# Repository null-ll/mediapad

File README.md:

# mediapad

A simple 3d printed volume/media controller macropad with 3 MX-style keyswitches and 8 customizable WS2812B RGB LEDs! Runs on [QMK firmware](https://github.com/qmk/qmk_firmware).

Case is still a WIP. Current version requires drilling holes into the top housing for the screws. The USB cutout also seems a bit off but that could just be poor tolerances from my 3d printer.

# usage

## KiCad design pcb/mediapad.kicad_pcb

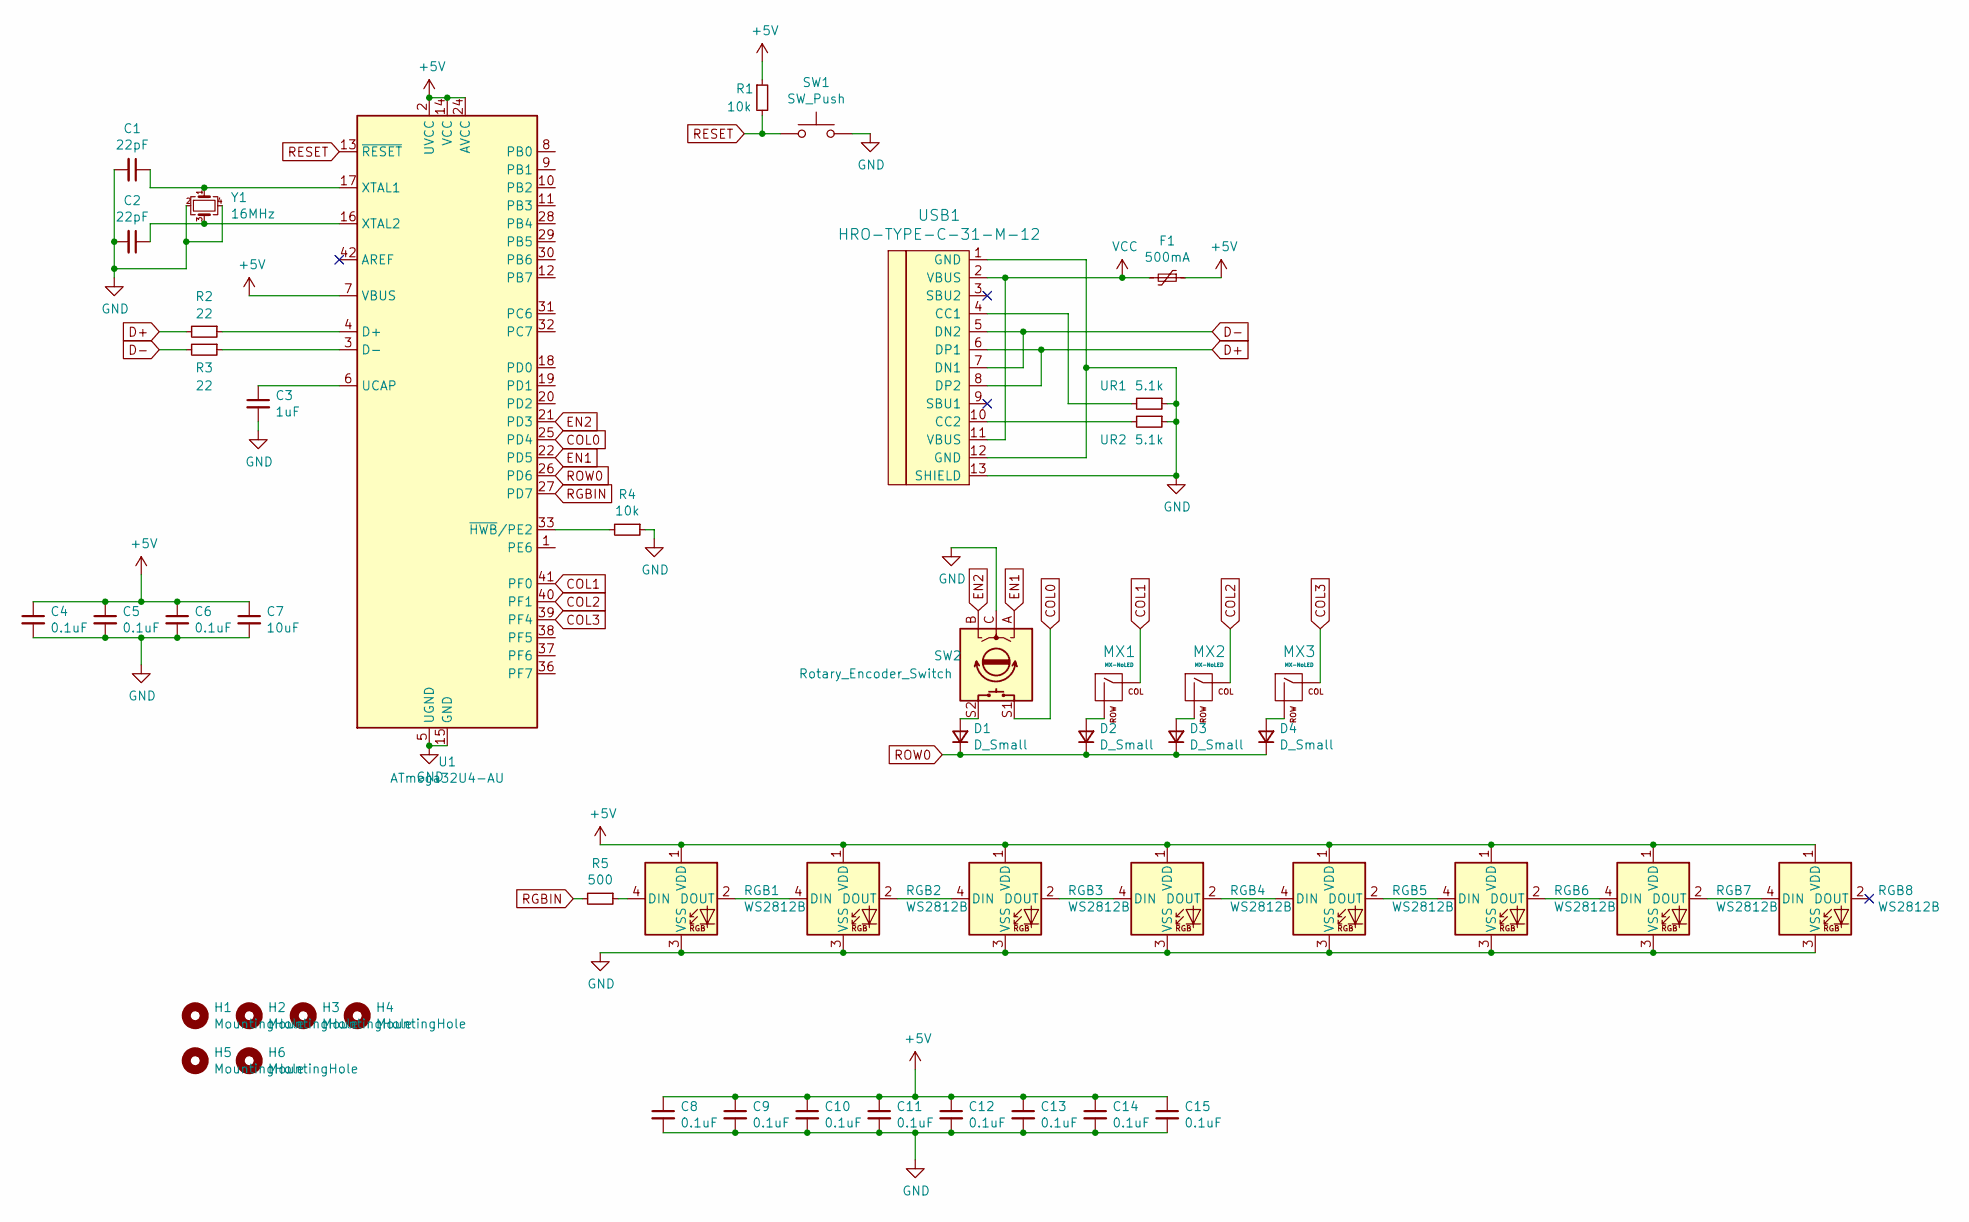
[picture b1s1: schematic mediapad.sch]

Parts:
C1, C2: 22pF; C_0805_2012Metric_Pad1.15x1.40mm_HandSolder
C3: 1uF; C_0805_2012Metric_Pad1.15x1.40mm_HandSolder
C4, C5, C6, C8, C9, C10, C11, C12, C13, C14, C15: 0.1uF; C_0805_2012Metric_Pad1.15x1.40mm_HandSolder
C7: 10uF; C_0805_2012Metric_Pad1.15x1.40mm_HandSolder
D1, D2, D3, D4: D_Small; D_SOD-123
F1: 500mA; Fuse_1206_3216Metric_Pad1.42x1.75mm_HandSolder
H1, H2, H3, H4, H5, H6: MountingHole; MountingHole_2.2mm_M2
MX1, MX2, MX3: MX-NoLED; MXOnly-1U-NoLED
R1, R4: 10k; R_0805_2012Metric_Pad1.15x1.40mm_HandSolder
R2, R3: 22; R_0805_2012Metric_Pad1.15x1.40mm_HandSolder
R5: 500; R_0805_2012Metric_Pad1.15x1.40mm_HandSolder
RGB1, RGB2, RGB3, RGB4, RGB5, RGB6, RGB7, RGB8: WS2812B; LED_WS2812B_PLCC4_5.0x5.0mm_P3.2mm
SW1: SW_Push; SW_SPST_SKQG_WithoutStem
SW2: Rotary_Encoder_Switch; RotaryEncoder_Alps_EC11E-Switch_Vertical_H20mm
U1: ATmega32U4-AU; TQFP-44_10x10mm_P0.8mm
UR1, UR2: 5.1k; R_0805_2012Metric_Pad1.15x1.40mm_HandSolder
USB1: HRO-TYPE-C-31-M-12; HRO-TYPE-C-31-M-12-HandSoldering
Y1: 16MHz; Crystal_SMD_3225-4Pin_3.2x2.5mm_HandSoldering

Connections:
+5V: C4.1, C5.1, C6.1, C7.1, C8.1, C9.1, C10.1, C11.1, C12.1, C13.1, C14.1, C15.1, F1.1, R1.1, RGB1.1 (VDD), RGB2.1 (VDD), RGB3.1 (VDD), RGB4.1 (VDD), RGB5.1 (VDD), RGB6.1 (VDD), RGB7.1 (VDD), RGB8.1 (VDD), U1.2 (UVCC), U1.7 (VBUS), U1.14 (VCC), U1.24 (AVCC), U1.34 (VCC), U1.44 (AVCC)
COL0: SW2.S1, U1.25 (PD4); also elsewhere on the board
COL1: MX1.1 (COL), U1.41 (PF0)
COL2: MX2.1 (COL), U1.40 (PF1)
COL3: MX3.1 (COL), U1.39 (PF4)
D+: R2.2, USB1.6 (DP1), USB1.8 (DP2); also elsewhere on the board
D-: R3.2, USB1.5 (DN2), USB1.7 (DN1); also elsewhere on the board
EN1: SW2.A, U1.22 (PD5); also elsewhere on the board
EN2: SW2.B, U1.21 (PD3); also elsewhere on the board
GND: C1.2, C2.2, C3.2, C4.2, C5.2, C6.2, C7.2, C8.2, C9.2, C10.2, C11.2, C12.2, C13.2, C14.2, C15.2, R4.1, RGB1.3 (VSS), RGB2.3 (VSS), RGB3.3 (VSS), RGB4.3 (VSS), RGB5.3 (VSS), RGB6.3 (VSS), RGB7.3 (VSS), RGB8.3 (VSS), SW1.2, SW2.C, U1.5 (UGND), U1.15 (GND), U1.23 (GND), U1.35 (GND), U1.43 (GND), UR1.1, UR2.1, USB1.1 (GND), USB1.12 (GND), USB1.13 (SHIELD), Y1.2, Y1.4; also elsewhere on the board
unnamed: C1.1, U1.17 (XTAL1), Y1.1
unnamed: C2.1, U1.16 (XTAL2), Y1.3
unnamed: C3.1, U1.6 (UCAP)
unnamed 13: D1.2 (A), SW2.S2; also elsewhere on the board
unnamed: D2.2 (A), MX1.2 (ROW)
unnamed: D3.2 (A), MX2.2 (ROW)
unnamed: D4.2 (A), MX3.2 (ROW)
unnamed: R2.1, U1.4 (D+)
unnamed: R3.1, U1.3 (D-)
unnamed: R4.2, U1.33 (~HWB~/PE2)
unnamed: R5.1, RGB1.4 (DIN)
unnamed: RGB1.2 (DOUT), RGB2.4 (DIN)
unnamed: RGB2.2 (DOUT), RGB3.4 (DIN)
unnamed: RGB3.2 (DOUT), RGB4.4 (DIN)
unnamed: RGB4.2 (DOUT), RGB5.4 (DIN)
unnamed: RGB5.2 (DOUT), RGB6.4 (DIN)
unnamed: RGB6.2 (DOUT), RGB7.4 (DIN)
unnamed: RGB7.2 (DOUT), RGB8.4 (DIN)
unnamed 47: UR1.2, USB1.10 (CC2); also elsewhere on the board
unnamed 48: UR2.2, USB1.4 (CC1); also elsewhere on the board
RESET: R1.2, SW1.1, U1.13 (~RESET); also elsewhere on the board
RGBIN: R5.2, U1.27 (PD7)
ROW0: D1.1 (K), D2.1 (K), D3.1 (K), D4.1 (K), U1.26 (PD6)
VCC: F1.2, USB1.2 (VBUS), USB1.11 (VBUS); also elsewhere on the board

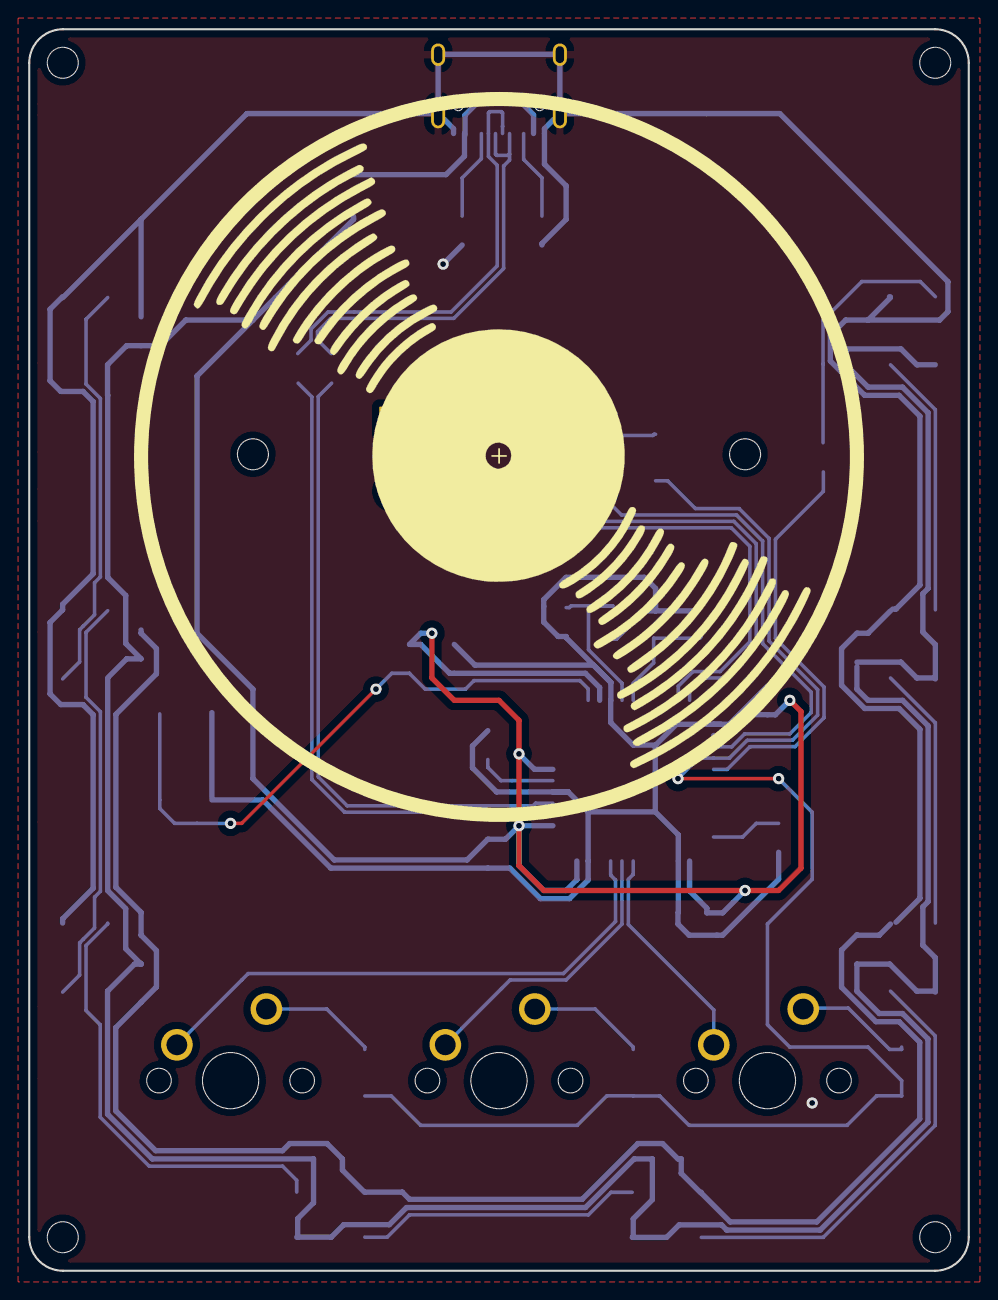
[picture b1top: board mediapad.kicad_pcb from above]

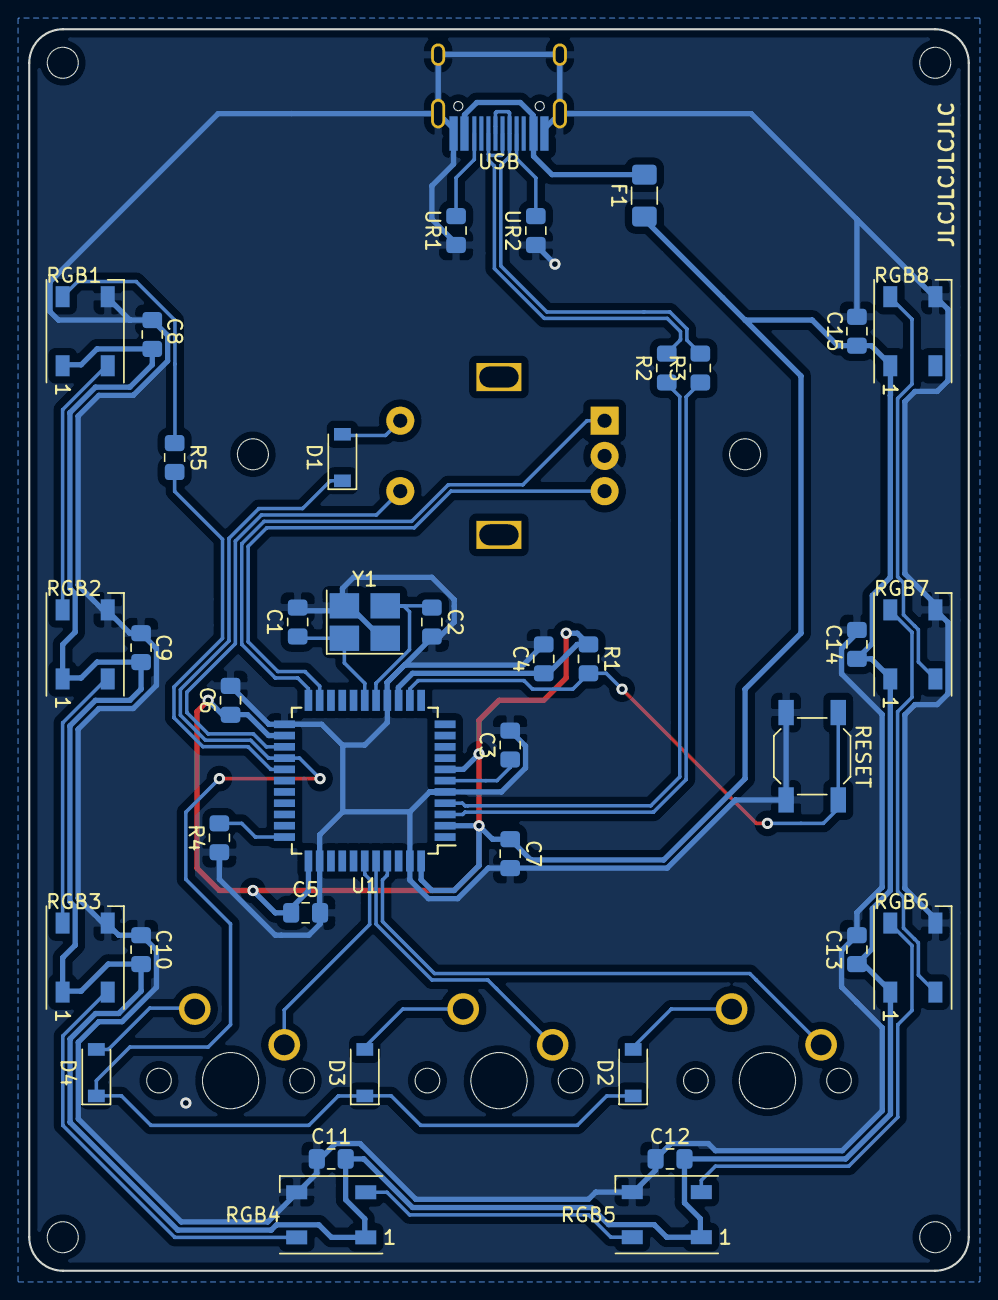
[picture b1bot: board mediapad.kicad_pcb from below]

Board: 2 copper layers, 66.7 x 88.1 mm, 49 parts (39 on the bottom side), 34 nets.

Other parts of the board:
RESET: SW_Push; SW_SPST_SKQG_WithoutStem
ROTARY ENCODER: Rotary_Encoder_Switch; RotaryEncoder_Alps_EC11E-Switch_Vertical_H20mm
USB: HRO-TYPE-C-31-M-12; HRO-TYPE-C-31-M-12-HandSoldering

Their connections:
COL0: ROTARY ENCODER.S1; also elsewhere on the board
D+: USB.6, USB.8; also elsewhere on the board
D-: USB.5, USB.7; also elsewhere on the board
EN1: ROTARY ENCODER.A; also elsewhere on the board
EN2: ROTARY ENCODER.B; also elsewhere on the board
GND: RESET.2, ROTARY ENCODER.C, USB.1, USB.12, USB.13; also elsewhere on the board
unnamed 13: ROTARY ENCODER.S2; also elsewhere on the board
unnamed 47: USB.10; also elsewhere on the board
unnamed 48: USB.4; also elsewhere on the board
RESET: RESET.1; also elsewhere on the board
VCC: USB.2, USB.11; also elsewhere on the board

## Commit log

2020-12-20 updated final pcb design
2020-12-20 add firmware files
